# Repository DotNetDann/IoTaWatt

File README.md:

### IotaWatt 4.8

This is forked from [boblemaire's github](https://github.com/boblemaire/IoTaWatt)

Changes to main repository:
* Changed the PCB to fit a ESP32 (In case one day) and to get the silk screen to show in the generated gurbers
* Created a sample config to integrate with HomeAssistant. This integration uses the rest sensor in HA and query’s the JSON data every few seconds. You are able to get all your channels as well as any output calculated values you have setup.

NOTE: The PCB s using a 1v refrence shunt so you need to edit the config.txt to add a refvolts item under the device.

>{
>	"device": {
>		"refvolts": 1.0,

Go to the main repository as boblemaire is doing some amazing work with this project.

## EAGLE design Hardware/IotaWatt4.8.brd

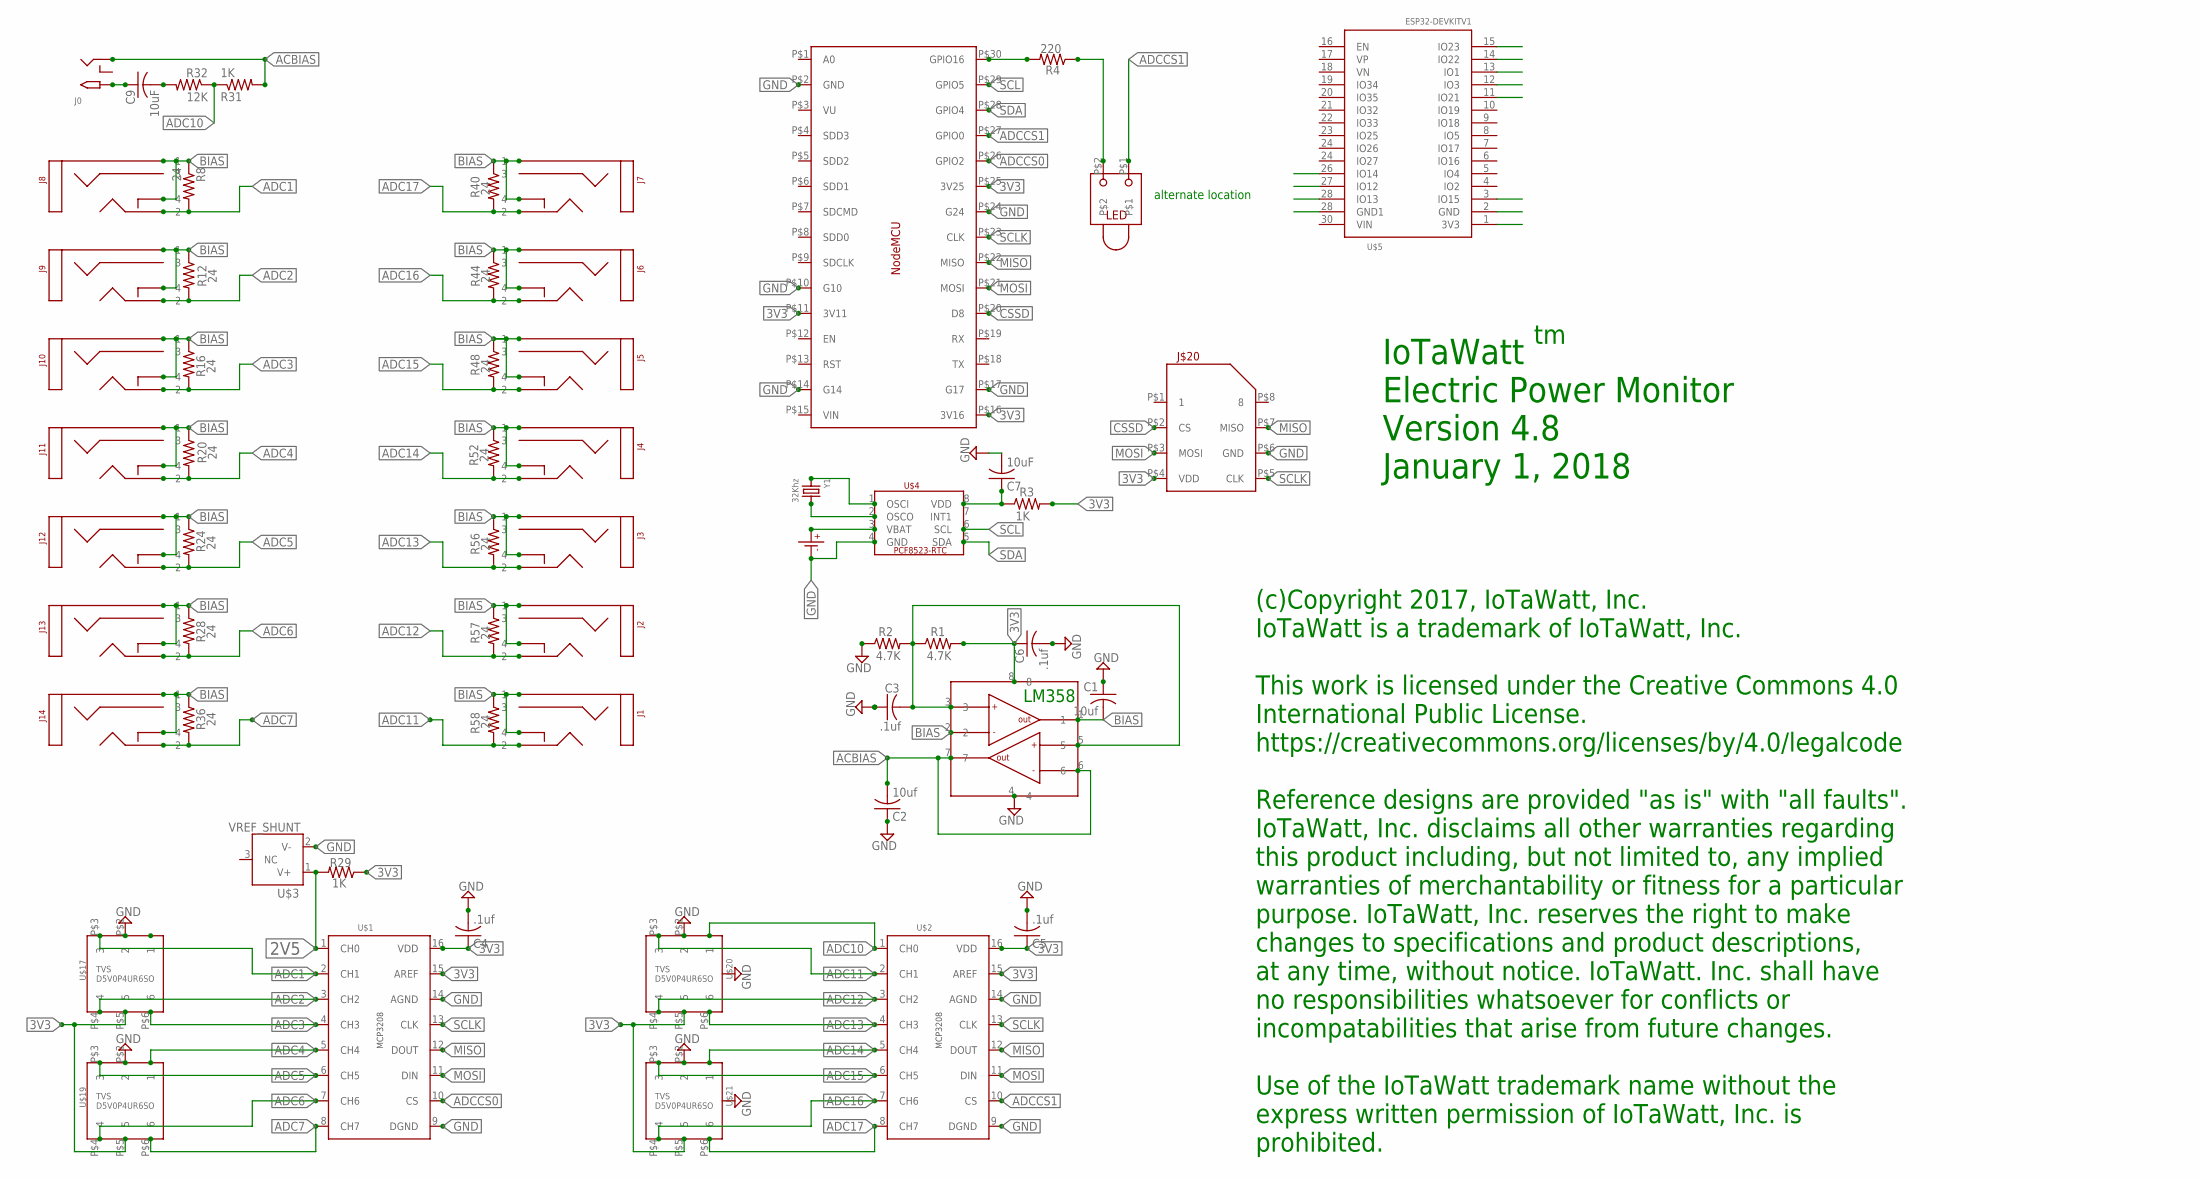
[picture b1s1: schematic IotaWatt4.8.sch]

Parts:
C1, C2: 10uf; C0805
C3, C4, C5, C6: .1uf; C0805
C7, C9: 10uF; C0805
J0: 2.1MMJACKSMT; DCJACK_2MM_SMT
J1, J2, J3, J4, J5, J6, J7, J8, J9, J10, J11, J12, J13, J14: STEREO_SMD; STEREO_SMT
J$20: MICROSD_PUSH/PULL; MICROSD
R1, R2: 4.7K; R0805
R3, R29, R31: 1K; R0805
R4: 220; R0805
R8, R12, R16, R20, R24, R28, R36, R40, R44, R48, R52, R56, R57, R58: 24; R0805
R32: 12K; R0805
U$1, U$2: MCP3208; SOIC_16
U$3: VREF_SHUNT; SOT23_3
U$4: PCF8523_RTC; SOIC_8
U$5: ESP32DEVKITV1; ESP32-DEVKITV1
U$16: NODEMCU
U$17, U$19, U$20, U$21: TVS_4CHAN_ARRAYSC-74; SC-74
U$18: CR1220SMD
U$22: LM358_DUAL_OP-AMP; SOIC_8
U$23: LED_RT_TRH; LED_TH_RT
Y1: 32Khz; CRYSTAL_8X3.8

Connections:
2V5: R29.2, U$1.1 (CH0), U$3.1 (V+)
3V3: C4.1, C5.1, C6.1, J$20.P$4 (VDD), R1.2, R3.2, R29.1, U$1.15 (AREF), U$1.16 (VDD), U$2.15 (AREF), U$2.16 (VDD), U$5.1 (3V3), U$16.P$11 (3V11), U$16.P$16 (3V16), U$16.P$25 (3V25), U$17.P$5 (5), U$19.P$5 (5), U$20.P$5 (5), U$21.P$5 (5), U$22.8
ACBIAS: C2.2, J0.GND (RING), R31.2, U$22.6, U$22.7
ADC1: J8.P$2 (2), R8.2, U$1.2 (CH1), U$17.P$3 (3)
ADC2: J9.P$2 (2), R12.2, U$1.3 (CH2), U$17.P$4 (4)
ADC3: J10.P$2 (2), R16.2, U$1.4 (CH3), U$17.P$6 (6)
ADC4: J11.P$2 (2), R20.2, U$1.5 (CH4), U$19.P$1 (1)
ADC5: J12.P$2 (2), R24.2, U$1.6 (CH5), U$19.P$3 (3)
ADC6: J13.P$2 (2), R28.2, U$1.7 (CH6), U$19.P$4 (4)
ADC7: J14.P$2 (2), R36.2, U$1.8 (CH7), U$19.P$6 (6)
ADC10: R31.1, R32.1, U$2.1 (CH0), U$20.P$1 (1)
ADC11: J1.P$2 (2), R58.2, U$2.2 (CH1), U$20.P$3 (3)
ADC12: J2.P$2 (2), R57.2, U$2.3 (CH2), U$20.P$4 (4)
ADC13: J3.P$2 (2), R56.2, U$2.4 (CH3), U$20.P$6 (6)
ADC14: J4.P$2 (2), R52.2, U$2.5 (CH4), U$21.P$1 (1)
ADC15: J5.P$2 (2), R48.2, U$2.6 (CH5), U$21.P$3 (3)
ADC16: J6.P$2 (2), R44.2, U$2.7 (CH6), U$21.P$4 (4)
ADC17: J7.P$2 (2), R40.2, U$2.8 (CH7), U$21.P$6 (6)
ADCCS0: U$1.10 (CS), U$5.11 (IO21), U$16.P$26 (GPIO2)
ADCCS1: U$2.10 (CS), U$5.12 (IO3), U$16.P$27 (GPIO0), U$23.P$1
BIAS: C1.2, J1.P$1 (1), J1.P$4 (4), J2.P$1 (1), J2.P$4 (4), J3.P$1 (1), J3.P$4 (4), J4.P$1 (1), J4.P$4 (4), J5.P$1 (1), J5.P$4 (4), J6.P$1 (1), J6.P$4 (4), J7.P$1 (1), J7.P$4 (4), J8.P$1 (1), J8.P$4 (4), J9.P$1 (1), J9.P$4 (4), J10.P$1 (1), J10.P$4 (4), J11.P$1 (1), J11.P$4 (4), J12.P$1 (1), J12.P$4 (4), J13.P$1 (1), J13.P$4 (4), J14.P$1 (1), J14.P$4 (4), R8.1, R12.1, R16.1, R20.1, R24.1, R28.1, R36.1, R40.1, R44.1, R48.1, R52.1, R56.1, R57.1, R58.1, U$22.1, U$22.2
CSSD: J$20.P$2 (CS), U$5.3 (IO15), U$16.P$20 (D8)
LED: R4.2, U$5.15 (IO23), U$16.P$30 (GPIO16)
MISO: J$20.P$7 (MISO), U$1.12 (DOUT), U$2.12 (DOUT), U$5.27 (IO12), U$16.P$22 (MISO)
unnamed: C7.1, R3.1, U$4.8 (VDD)
unnamed: R4.1, U$23.P$2
unnamed: C9.2, R32.2
unnamed: C9.1, J0.PWR2 (TIP)
unnamed: U$4.3 (VBAT), U$18.P+ (P$+)
unnamed: U$4.2 (OSCO), Y1.P$4 (2)
unnamed: U$4.1 (OSCI), Y1.P$1 (1)
SCL: U$4.6 (SCL), U$5.14 (IO22), U$16.P$29 (GPIO5)
SCLK: J$20.P$5 (CLK), U$1.13 (CLK), U$2.13 (CLK), U$5.26 (IO14), U$16.P$23 (CLK)
SDA: U$4.5 (SDA), U$5.13 (IO1), U$16.P$28 (GPIO4)
VREF: C3.2, R1.1, R2.2, U$22.3, U$22.5

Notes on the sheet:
IoTaWatt Electric Power Monitor Version 4.8 January 1, 2018
alternate location
LM358
(c)Copyright 2017, IoTaWatt, Inc. IoTaWatt is a trademark of IoTaWatt, Inc. This work is licensed under the Creative Commons 4.0 International Public License. https://creativecommons.org/licenses/by/4.0/legalcode Reference designs are provided "as is" with "all faults". IoTaWatt, Inc. disclaims all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

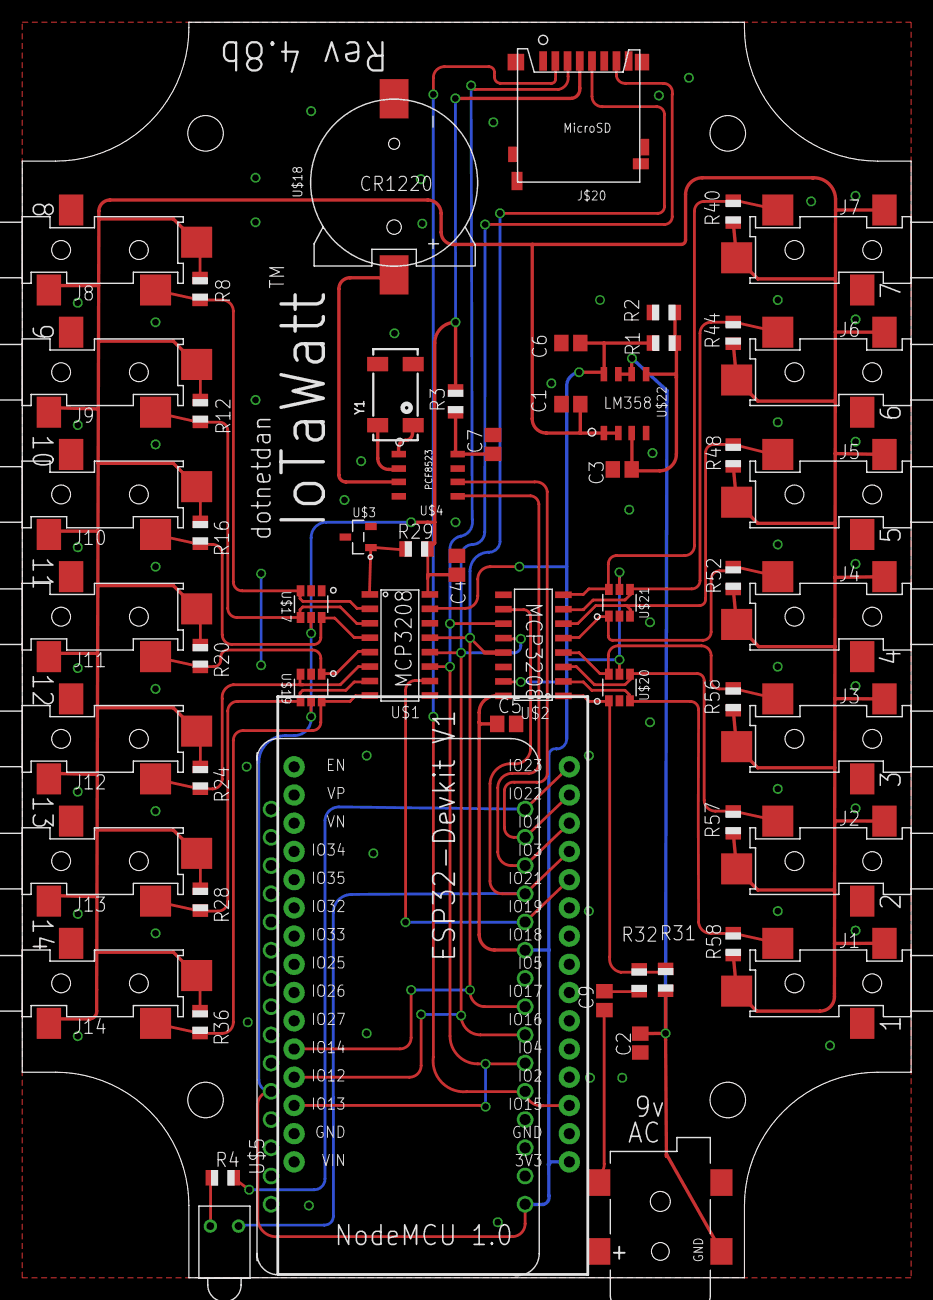
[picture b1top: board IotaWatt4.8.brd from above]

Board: 2 copper layers, 80.0 x 113.0 mm, 59 parts (0 on the bottom side), 37 nets.

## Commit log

2018-12-11 Post my changes again

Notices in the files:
parts and their libraries:
microbuilder: This work is placed in the public domain, and may be freely used for commercial and non-commercial work with the following conditions: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
